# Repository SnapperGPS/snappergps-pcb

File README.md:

> *Are you looking for the open-source SnapperGPS hardware design files? You can find the files for the original version V1.0.0 in this repository and the files for an updated version V2.0.0 [in another repository](https://github.com/SnapperGPS/snappergps-pcb-2). For differences between both versions, please refer to the documentation over there. Jonas, May 2023*

# snappergps-pcb

The SnapperGPS receiver is a small, low-cost, and low-power GNSS receiver for non-real-time wildlife tracking. It employs the snapshot GNSS technology, which offloads the computationally expensive data processing to the cloud, and:

* Measures 32.0 mm x 27.3 mm,

* Operates for more than a year on a tiny 40 mAh battery,

* Has enough memory to provide almost 11,000 position fixes,

* Captures fixes in user-defined time intervals or externally triggered,

* Needs only 12 ms of signal reception for a fix,

* Employs multiple satellite systems for high reliability (GPS, Galileo, and BeiDou),

* Achieves a median real-world tracking accuracy of about 12 m (before smoothing),

* Maintains a real-time clock to accurately timestamp the fixes,

* Measures the temperature in addition, and

* Is configured via USB in your browser without the need to install a driver or an app.

This repository contains the hardware design files that can be used to replicate a SnapperGPS receiver.

If you use SnapperGPS hardware or software for research, please consider citing our publications.

For the hardware:

> Jonas Beuchert, Amanda Matthes, and Alex Rogers. 2023. SnapperGPS: Open Hardware for Energy-Efficient, Low-Cost Wildlife Location Tracking with Snapshot GNSS. Journal of Open Hardware, 7(1): 2, pp. 1–13. [https://doi.org/10.5334/joh.48](https://openhardware.metajnl.com/articles/10.5334/joh.48/).

For the cloud-processing software:

> Jonas Beuchert and Alex Rogers. 2021. SnapperGPS: Algorithms for Energy-Efficient Low-Cost Location Estimation Using GNSS Signal Snapshots. In SenSys ’21: ACM Conference on Embedded Networked Sensor Systems, November, 2021, Coimbra, Portugal. ACM, New York, NY, USA, 13 pages. https://doi.org/10.1145/3485730.3485931.

**Table of Contents**

1. [Workflow](#workflow)

2. [Getting started](#getting-started)

3. [Repository Structure](#repository-structure)

4. [Professional Manufacturing](#professional-manufacturing)

5. [Hand Assembly](#hand-assembly)

6. [Testing](#testing)

7. [Hardware Overview](#hardware-overview)

8. [Pinout](#pinout)

9. [Bill of Materials](#bill-of-materials)

10. [Additional Resources](#additional-resources)

11. [Acknowledgements](#acknowledgements)

## Workflow

- Get/build your SnapperGPS receiver (see sections below).
- [Configure](https://snappergps.info/configure) your SnapperGPS receiver in your browser for your deployment.
- Deploy your SnapperGPS receiver.
- The SnapperGPS receiver captures GNSS snapshots according to your configuration.
- Recover your SnapperGPS receiver.
- [Upload](https://snappergps.info/upload) the data from your SnapperGPS receiver to our server.
- [Download](https://snappergps.info/view) the track of your surveilled animal.

## Getting started

You already have a SnapperGPS receiver? See [here](GETTING-STARTED.md) how to get started.

You need to build one first? Keep reading.

## Repository Structure

The two files `.brd` and `.sch` are CAD files that contain the PCB's board design and schematic, respectively. They have been created with Autodesk EAGLE 9.6.2, but should be compatible with other electronic design software.

The table `.csv` contains the bill of materials (BOM).

The directory `CAMOutputs` includes the Gerber files and drill file, which are necessary for PCB manufacturing.

The two files `.mnb` and `.mnt` can be used for a pick-and-place machine and describe the component positions and orientations on the bottom and top layer, respectively.

## Professional Manufacturing

The simplest way to replicate SnapperGPS is to upload the BOM, the Gerber files, the drill file, and the pick and place files to an online PCB manufacturing and assembly service. They will source the components, print the PCB, and assemble the board.

We recommend a thickness between 0.8 and 1.6 mm for the two-layered board. The substrate can be FR-4 and hot air solder levelling (HASL) or electroless nickel immersion gold (ENIG) can be used for the finish.

You can find an FAQ on professional manufacturing in [the discussions forum](https://github.com/orgs/SnapperGPS/discussions/22).

## Hand Assembly

An alternative to prefessional manufacturing is to just obtain the SnapperGPS PCB from a PCB manufacturer and to manually assembly the board.
Hand-soldering a board takes less than 2 h for a skilled person, but requires intermediate equipment and skills and potentially additional time for testing, debugging, and re-work.

A laser-cut stencil for applying the solder paste can be helpful and can often be ordered together with the PCB.
In addition, the following materials and equipment are required:

* Soldering paste

* Syringe

* Spatula

* Tweezers

* Hot plate, re-flow oven, or hot air gun

* Flux pen (optional, for re-work)

* Multi-meter (optional, for debugging)

Proceed with the following steps to assemble a SnapperGPS PCB:

* Rigidly fix the PCB to a surface with the top layer pointing up.

* Fix the stencil on the PCB.

* Use the syringe to apply solder paste to the stencil.

* Use the spatula to distribute the solder paste such that all pads on the PCB are covered.

* Remove the stencil.

* Check that all pads are covered with solder paste.

* If not, manually apply solder paste.

* Use tweezers to place the components on the PCB.

* Heat the PCB following the re-flow profile of the used solder paste.

* Test the PCB (see below).

* If it does not work, identify problematic PCB sections and re-work, e.g., by applying flux and re-flowing the board. The most common issues are shorts and missing solder paste on some pads, which can be identified by using a multi-meter for continuity testing, but it is also possible that a component is placed incorrectly.

|  | 
|:--:| 
| *Figure 1: Several SnapperGPS PCBs ready for hand assembly.* |

|  | 
|:--:| 
| *Figure 2: A stencil on top of a SnapperGPS PCB with solder paste applied to it.* |

|  | 
|:--:| 
| *Figure 3: A SnapperGPS PCB with solder paste and components on a hot plate while re-flowing.* |

|  | 
|:--:| 
| *Figure 4: An assembled SnapperGPS receiver.* |

|  | 
|:--:| 
| *Figure 5: Measuring the current consumption of an assembled SnapperGPS receiver (bottom left) with a multi-meter (right), a DC voltage source (centre), two jumper wires, and alligator clips.* |

|  | 
|:--:| 
| *Figure 6: Charging a 110 mAh lithium-ion polymer battery via USB with a *SparkFun LiPo Charger Basic*.* |

|  | 
|:--:| 
| *Figure 7: Testing a SnapperGPS receiver with the SnapperGPS app on an Android smartphone using a USB-C cable.* |

## Testing

If you replicated a SnapperGPS receiver yourself, you need to flash the SnapperGPS firmware first:

* Short the VDD pin and the SWCLK pin of the SnapperGPS receiver, e.g., with a paper clip.

* Connect the SnapperGPS receiver via a USB-C cable to a host computer.

* Download [the SnapperGPS firmware binary](https://github.com/SnapperGPS/snappergps-firmware/releases).

* Install [the AudioMoth Flash App](https://github.com/OpenAcousticDevices/AudioMoth-Flash-App/releases) **or** [the Silicon Labs Simplicity Commander](https://community.silabs.com/s/article/simplicity-commander).

* Use one of the two tools two flash the firmware binary to the SnapperGPS receiver. (If you use the AudioMoth Flash App, either use v1.4.0 or, if you use v1.6.0, then disable "Clear User Data When Flashing".)

* Remove the paper clip.

Now, you can continue with some basic testing:

* Open [the SnapperGPS web app](https://snappergps.info) in Microsoft Edge or Google Chrome or download it from [the Microsoft Store](https://apps.microsoft.com/store/detail/snappergps/9P9RPRS6LSMM) or [Google Play](https://play.google.com/store/apps/details?id=com.herokuapp.snapper_gps.twa). (Alternatively, you can also host the SnapperGPS web app yourself, as described in [the _snappergps-app_ repository](https://github.com/SnapperGPS/snappergps-app)).

* Go to the *Configure* page and click/tap on *Pair receiver*.

* The connected SnapperGPS receiver should now be selectable in a pop-up window.

* After pairing, confirm that the receiver information in the table on the top of the page is appropriate, including on-board time and firmware version. The snapshot count should be zero.

* Connect a LiPo battery to the SnapperGPS receiver, paying attention to the polarity markers on top of the PCB. Connect the black cable to the pin next to the *-* and the red cable to the pin next to the *+*.

* Check the measured battery voltage in the table at the top of the *Configure* page. We recommend charging the battery to at least 4.1 V before a long-term deployment.

* Connnect an active GNSS antenna of your choice via the U.FL connector to the SnapperGPS receiver.

* Select some configuration parameters in the app and click/tap on *Configure*.

* Disconnect the SnapperGPS receiver.

* Record a few snapshots outdoors.

* Reconnect the SnapperGPS receiver.

* Go to the *Upload* page and follow the instructions to upload the snapshots from the SnapperGPS receiver to the server. Please select only snapshots for processing that you collected outdoors.

* Once processing is complete, inspect the calculated track on the *Download* page. There are also links to some of our tracks for comparison.

Testing the localisation accuracy:

* Record some data outdoors at a location with known coordinates.

* Upload it via the SnapperGPS app.

* Calculate the horizontal error between the estimated locations and the ground truth.

* We obtained median errors of 10-12 m, depending on the scenario.

Measuring the power consumption:

* Configure a SnapperGPS receiver using the SnapperGPS app.

* Power the SnapperGPS receiver from an external DC source with 3.7-4.2 V.

* Place an ammeter in series with the source.

* The current should be 1-2 μA if the board is sleeping and the maximum current should be around 25 mA when capturing a snapshot. The charge consumption for a single snapshot should be <0.3 μAh.

Testing the flash memory:

* Record the maximum of 10901 snapshots.

* Transfer them to a host computer using the *Transfer data* button on the *Upload* page of the SnapperGPS web app.

* Ensure that all 10901 snapshots have been transferred and are provided as download.

## Hardware Overview

Please have a look at our [paper](https://doi.org/10.5334/joh.48).

## Pinout

We expose the three general-purpose input/output pins (GPIOs) PA0, PA1, and PA2 of the MCU as well as the supply voltage pin VDD and the ground pin GND at an edge of the PCB.
This allows to connect external modules to extend the functionality of the device.
This can be done by soldering wires on the rectangular pads.
For the functionality of the three pins, please refer to [the pinout section in the datasheet of the EFM32HG310](https://www.silabs.com/documents/public/data-sheets/efm32hg-datasheet.pdf#page=118).

We also expose the VDD, GND, RESET, SWCLK, and SWDIO pins of the MCU on the back of the PCB.
The last two ones allow for debugging or flashing using [Serial Wire Debug (SWD)](https://community.silabs.com/s/article/serial-wire-debug-swd-x).
All five circular pads have a spacing of 0.1 in and, hence, the same as common PCB headers.

All ten pads are labelled on the silkscreen of the PCB.

```
Front           │           │ Back
                │           │
                │           │ ○ GND
          VDD □ │           │
                │           │ ○ RESET
    GPIO3/PA2 □ │           │
                │           │ ○ SWCLK
    GPIO2/PA1 □ │           │
                │           │ ○ SWDIO
    GPIO1/PA0 □ │           │
                │           │ ○ VDD
          GND □ │           │
────────────────┘           │
```

## Bill of Materials

|Designator                                    |Qty|Manufacturer                  |Part #                                 |Description/Value                                            |Package/Footprint|Mounting Type|Notes                                                                          |Supplier URL                                                                                           |
|----------------------------------------------|--:|------------------------------|---------------------------------------|-------------------------------------------------------------|-----------------|-------------|-------------------------------------------------------------------------------|-------------------------------------------------------------------------------------------------------|
|C4, C8, C10, C12, C13, C14, C16, C17, C20, C23| 10|Murata                        |GRM155R60J104KA01D                     |Ceramic capacitor, 100 nF                                    |0402             |SMD          |                                                                               |https://www.digikey.com/en/products/detail/murata-electronics/GRM155R60J104KA01D/490-6287-1-ND/3845484 |
|C3, C5, C6, C7, C9                            |  5|Murata                        |GRM155R60J103KA01D                     |Ceramic capacitor, 10 nF                                     |0402             |SMD          |                                                                               |https://www.digikey.com/en/products/detail/murata-electronics/GRM155R60J103KA01D/490-6286-1-ND/3845483 |
|C2                                            |  1|Murata                        |GRM1555C1H101JA01J                     |Ceramic capacitor, 100 pF                                    |0402             |SMD          |                                                                               |https://www.digikey.com/en/products/detail/murata-electronics/GRM1555C1H101JA01J/490-7754-1-ND/4358006 |
|C1                                            |  1|Murata                        |GRM1555C1H220JA01D                     |Ceramic capacitor, 22 pF                                     |0402             |SMD          |                                                                               |https://www.digikey.com/en/products/detail/murata-electronics/GRM1555C1H220JA01D/490-5868-1-ND/3175200 |
|C21, C22                                      |  2|Murata                        |GRM1555C1H180JA01D                     |Ceramic capacitor, 18 pF                                     |0402             |SMD          |                                                                               |https://www.digikey.com/en/products/detail/murata-electronics/GRM1555C1H180JA01D/2854383               |
|C11, C19, C24, C25                            |  4|Murata                        |GRM188R60J105KA01D                     |Multi-layer ceramic capacitor, 1 uF, 6.3 V, X5R              |0603             |SMD          |                                                                               |https://www.digikey.com/en/products/detail/murata-electronics/GRM188R60J105KA01D/490-1550-1-ND/587755  |
|C18                                           |  1|Murata                        |GRM185R60J475ME15D                     |Multi-layer ceramic capacitor, 4.7 uF, 6.3 V, X5R            |0603             |SMD          |                                                                               |https://www.digikey.com/en/products/detail/murata-electronics/GRM185R60J475ME15D/490-3892-1-ND/965934  |
|C15                                           |  1|Murata                        |GRM188R60J106KE47D                     |Multi-layer ceramic capacitor, 10 uF, 6.3 V, X5R             |0603             |SMD          |                                                                               |https://www.digikey.com/en/products/detail/murata-electronics/GRM188R60J106KE47D/490-12538-1-ND/5797528|
|L1                                            |  1|Delta Electronics             |0402HS-390EKTS                        |Fixed inductor, 39 nH, 200 mA, 550 MOhm                      |0402             |SMD          |                                                                               |https://www.digikey.com/en/products/detail/0402HS-390EKTS/2035-0402HS-390EKTSCT-ND/10231211            |
|L2                                            |  1|Murata                        |BLM15HB221SH1D                         |Ferrite bead                                                 |0402             |SMD          |                                                                               |https://www.digikey.com/en/products/detail/murata-electronics/BLM15HB221SH1D/6798444                   |
|R11, R12                                      |  2|Yageo                         |RC0402FR-0715RL                        |Resistor, 15R                                                |0402             |SMD          |                                                                               |https://www.digikey.com/en/products/detail/yageo/RC0402FR-0715RL/311-15LRCT-ND/2827914                 |
|R15, R16                                      |  2|Yageo                         |RC0402FR-071KL                         |Resistor, 1K                                                 |0402             |SMD          |                                                                               |https://www.digikey.com/en/products/detail/yageo/RC0402FR-071KL/726513                                 |
|R10, R13, R17                                 |  3|Yageo                         |RC0402FR-074K7L                        |Resistor, 4K7                                                |0402             |SMD          |                                                                               |https://www.digikey.com/en/products/detail/yageo/RC0402FR-074K7L/311-4-7KLRCT-ND/2827881               |
|R7, R8                                        |  2|Yageo                         |RC0402FR-075K1L                        |Resistor, 5K1                                                |0402             |SMD          |                                                                               |https://www.digikey.com/en/products/detail/yageo/RC0402FR-075K1L/726624                                |
|R18                                           |  1|Yageo                         |RC0402FR-076K8L                        |Resistor, 6K8                                                |0402             |SMD          |                                                                               |https://www.digikey.com/en/products/detail/yageo/RC0402FR-076K8L/311-6-80KLRCT-ND/729589               |
|R14, R19                                      |  2|Yageo                         |RC0402FR-0710KL                        |Resistor, 10K                                                |0402             |SMD          |                                                                               |https://www.digikey.com/en/products/detail/yageo/RC0402FR-0710KL/726523                                |
|R1, R2, R3, R4, R5, R6, R9                    |  7|Yageo                         |RC0402FR-07100KL                       |Resistor, 100K                                               |0402             |SMD          |                                                                               |https://www.digikey.com/en/products/detail/yageo/RC0402FR-07100KL/311-100KLRCT-ND/729473               |
|Q2                                            |  1|Jauch Quartz                  |Q 0,032768-JTX310-12,5-10-T1-HMR-50K-LF|Crystal, 32.768 kHz ±10 ppm, 12.5 pF, 50 kOhm                |2-SMD            |SMD          |Possible substitutes: Epsom, X1A0001410004 FC-135R 32.768KHZ 9PF or Jauch Quartz, Q 0,032768-JTX310-12,5-10-T1-HMR-60K-LF|https://www.digikey.com/en/products/detail/jauch-quartz/Q-0-032768-JTX310-12-5-10-T1-HMR-50K-LF/8108077|
|D1                                            |  1|Rohm Semiconductor            |SML-D12M1WT86                          |LED, yellow-green, 572 nm, 2.2 V                             |0603             |SMD          |                                                                               |https://www.digikey.com/en/products/detail/rohm-semiconductor/SML-D12M1WT86/SML-D12M1WT86CT-ND/5843861 |
|D2                                            |  1|Rohm Semiconductor            |SML-D12U1WT86                          |LED, red, 620 nm, 2.2 V                                      |0603             |SMD          |                                                                               |https://www.digikey.com/en/products/detail/rohm-semiconductor/SML-D12U1WT86/SML-D12U1WT86CT-ND/5843858 |
|TCXO1                                         |  1|Connor Winfield               |D32G-016.368M                          |Temperature compensated oscillator, 16.384 MHz               |3.2x2.5          |SMD          |Possible substitutes: EPSON, X1G005441030112 or TXC Corporation, 7Q-16.368MBG-T|https://www.digikey.com/en/products/detail/connor-winfield/D32G-016-368M/3641696                       |
|U2                                            |  1|Skyworks Solutions Inc.       |SE4150L-R                              |RF receiver                                                  |24-QFN           |SMD          |                                                                               |https://www.digikey.com/en/products/detail/skyworks-solutions-inc/SE4150L-R/863-1354-1-ND/2745473      |
|SAW1                                          |  1|Abracon LLC                   |AFS20A42-1575.42-T3                    |SAW filter, 1.575 GHz, BW 42 MHz                             |4-SMD            |SMD          |Possible substitute: AFS20A02-1575.42-T3                                       |https://www.digikey.com/en/products/detail/abracon-llc/AFS20A42-1575-42-T3/535-12069-1-ND/4075659      |
|U1                                            |  1|Silicon Labs                  |EFM32HG310F64G-C-QFN32R                |Microcontroller                                              |32-QFN           |SMD          |Possible substitutes: EFM32HG310F64G-A-QFN32R or EFM32HG310F64G-B-QFN32R       |https://www.digikey.com/en/products/detail/silicon-labs/EFM32HG310F64G-C-QFN32R/336-6165-1-ND/10314104 |
|U3                                            |  1|Nexperia                      |PRTR5V0U2AX,235                        |TVS diode, 5.5 V                                             |SOT143B          |SMD          |                                                                               |https://www.digikey.com/en/products/detail/nexperia-usa-inc/PRTR5V0U2AX235/1727-5862-1-ND/2698064      |
|IC1                                           |  1|Winbond Electronics           |W25N512GVEIG                           |NAND flash, 512 Mbit                                         |WSON-8           |SMD          |                                                                               |https://www.digikey.com/en/products/detail/W25N512GVEIG/256-W25N512GVEIG-ND/12143334                   |
|J3                                            |  1|TE Connectivity AMP Connectors|1909763-1                              |U.FL connector jack, 50 Ohm                                  |                 |SMD          |                                                                               |https://www.digikey.com/en/products/detail/1909763-1/A118077CT-ND/4729711                              |
|Q1, Q3, Q4                                    |  3|Rohm Semiconductor            |TT8M1TR                                |Mosfet array N and P-channel, 20 V, 2.5 A, 1 W               |8-SMD            |SMD          |                                                                               |https://www.digikey.com/en/products/detail/rohm-semiconductor/TT8M1TR/5042837                          |
|U4                                            |  1|ABLIC U.S.A. Inc.             |S-1318D33-M5T1U4                       |Linear voltage regulator IC, positive fixed, 1 output, 100 mA|SOT-23-5         |SMD          |                                                                               |https://www.digikey.com/en/products/detail/ablic-inc/S-1318D33-M5T1U4/10313979                         |
|J1                                            |  1|JAE Electronics               |DX07S016JA1R1500                       |USB-C receptacle connector, 24 Pins (16+8 dummy), right angle|                 |through-hole |                                                                               |https://www.digikey.com/en/products/detail/jae-electronics/DX07S016JA1R1500/11585731                   |
|J2                                            |  1|JST Sales America Inc.        |S2B-PH-SM4-TB                          |Connector header, right angle, 2 position, 2.00 mm           |                 |SMD          |                                                                               |https://www.digikey.com/en/products/detail/jst-sales-america-inc/S2B-PH-SM4-TB-LF-SN/926655            |
|                                              |   |                              |                                       |                                                             |                 |             |                                                                               |                                                                                                       |

The BOM differs slightly from the one for initial SnapperGPS test boards, which was only $14 in a batch of 100.
For example, we used cheaper TCXOs, the X1G005441030112 manufactured by EPSON or the 7Q-16.368MBG-T from the TXC Corporation, which cost around $2 instead of the expensive D32G-016.368M that costs $7-$8.
We had to introduce this change because of the on-going global supply chain disruptions and recommend to revert to one of the initial choices for replications, if possible, to reduce the overall cost.

## Additional resources

## Acknowledgements

SnapperGPS is developed by
[Jonas Beuchert](https://users.ox.ac.uk/~kell5462/),
[Amanda Matthes](https://amanda-matthes.github.io/), and
[Alex Rogers](https://www.cs.ox.ac.uk/people/alex.rogers/)
in the Department of Computer Science
of the University of Oxford.

Jonas Beuchert and Amanda Matthes are
funded by the EPSRC Centre for Doctoral Training in
Autonomous Intelligent Machines and Systems
(DFT00350-DF03.01, DFT00350-DF03.05) and develop
SnapperGPS as part of their doctoral studies.
The implementation of SnapperGPS 
was co-funded by an EPSRC IAA Technology Fund
(D4D00010-BL14).

[Amanda Matthes](https://github.com/amanda-matthes) owns the copyright of the current SnapperGPS logo/icon that is on the bottom layer silkscreen of the PCB.

##

This documentation is licensed under a
[Creative Commons Attribution 4.0 International License][cc-by].

[![CC BY 4.0][cc-by-image]][cc-by]

[cc-by]: http://creativecommons.org/licenses/by/4.0/
[cc-by-image]: https://i.creativecommons.org/l/by/4.0/88x31.png

SnapperGPS V1.0.0 is certified as open source hardware by the Open Source Hardware Association with UID [UK000044](https://certification.oshwa.org/uk000044.html).

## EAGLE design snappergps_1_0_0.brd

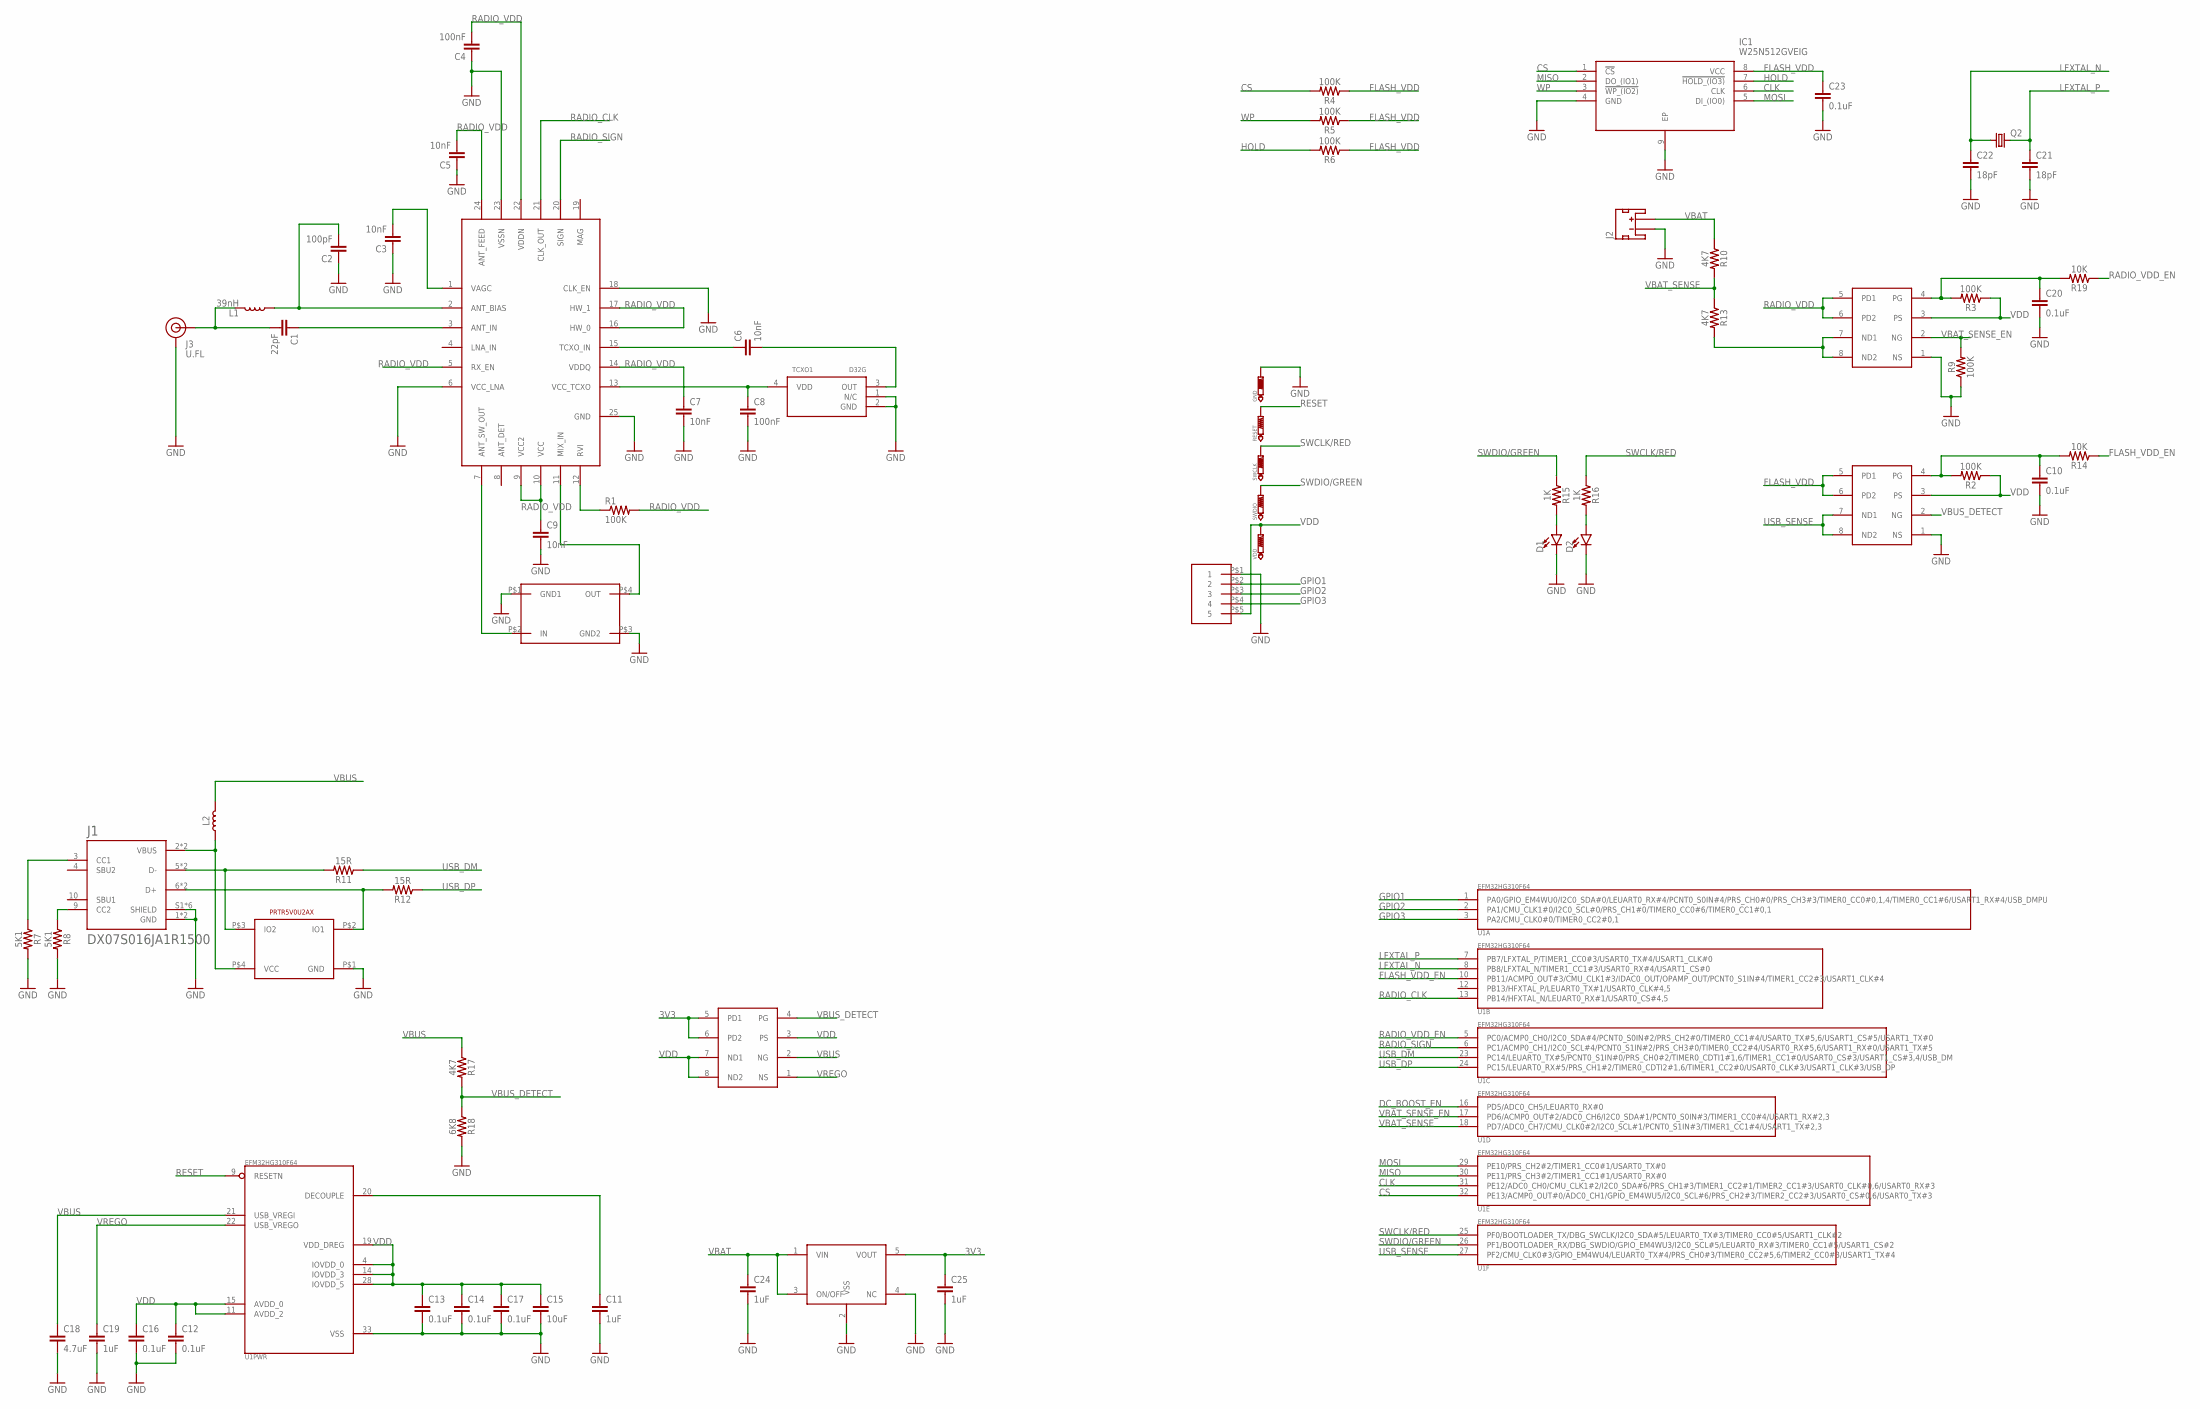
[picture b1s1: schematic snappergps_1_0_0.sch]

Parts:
C1: 22pF; 0402
C2: 100pF; 0402
C3, C5, C6, C7, C9: 10nF; 0402
C4, C8: 100nF; 0402
C10, C12, C13, C14, C16, C17, C20, C23: 0.1uF; 0402
C11, C19, C24, C25: 1uF; 0603
C15: 10uF; 0603
C18: 4.7uF; 0603
C21, C22: 18pF; 0402
D1, D2: LED0603; LED-0603
GND: PTR1B1,27; B1,27
IC1: W25N512GVEIG; SON127P800X600X80-9N
J1: DX07S016JA1R1500; JAE_DX07S016JA1R1500
J2: JST_2MM_MALE; JST-2-SMD
J3: U.FL
L1: 39nH; 0402
L2: INDUCTOR; 0402
Q1, Q3, Q4: TT8M1TRAMANDA; AMANDA_TSST8
Q2: CRYSTAL_JTX310; 3.2X1.5
R1, R2, R3, R4, R5, R6, R9: 100K; 0402
R7, R8: 5K1; 0402
R10, R13, R17: 4K7; 0402
R11, R12: 15R; 0402
R14, R19: 10K; 0402
R15, R16: 1K; 0402
R18: 6K8; 0402
RESET: PTR1B1,27; B1,27
SAW1: SAW_FILTER
SWCLK: PTR1B1,27; B1,27
SWDIO: PTR1B1,27; B1,27
TCXO1: D32G
U1: EFM32HG310F64; QFN32
U2: RF_CIRCUIT-SE4150L; QFN50P400X400X90-25N
U3: TVS_DIODE-PRTR5V0U2AX
U4: S-1318D33-M5T1U4; SOT95P280X145-5N
U5: ALEX_CONN5
VDD: PTR1B1,27; B1,27

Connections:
3V3: C25.1, Q4.5 (PD1), Q4.6 (PD2), U4.5 (VOUT)
CLK: IC1.6 (CLK), U1.31 (PE12/ADC0_CH0/CMU_CLK1#2/I2C0_SDA#6/PRS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)
CS: IC1.1 (!CS), R4.2, U1.32 (PE13/ACMP0_OUT#0/ADC0_CH1/GPIO_EM4WU5/I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)
DC_BOOST_EN: U1.16 (PD5/ADC0_CH5/LEUART0_RX#0)
FLASH_VDD: C23.1, IC1.8 (VCC), Q3.5 (PD1), Q3.6 (PD2), R4.1, R5.1, R6.1
FLASH_VDD_EN: R14.1, U1.10 (PB11/ACMP0_OUT#3/CMU_CLK1#3/IDAC0_OUT/O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)
GND: C2.1, C3.1, C4.1, C5.1, C7.2, C8.2, C9.2, C10.2, C11.2, C12.2, C13.2, C14.2, C15.2, C16.2, C17.2, C18.2, C19.2, C20.2, C21.2, C22.2, C23.2, C24.2, C25.2, D1.C, D2.C, GND.TP, IC1.4 (GND), IC1.9 (EP), J1.1 (GND), J1.12 (GND), J1.S1 (SHIELD), J1.S2 (SHIELD), J1.S3 (SHIELD), J1.S4 (SHIELD), J1.S5 (SHIELD), J1.S6 (SHIELD), J2.1 (-), J3.1 (GND), J3.2 (GND), Q1.1 (NS), Q3.1 (NS), R7.2, R8.2, R9.1, R18.2, SAW1.P$1 (GND1), SAW1.P$3 (GND2), TCXO1.1 (N/C), TCXO1.2 (GND), U1.33 (VSS), U2.6 (VCC_LNA), U2.18 (CLK_EN), U2.23 (VSSN), U2.25 (GND), U3.P$1 (GND), U4.2 (VSS), U4.4 (NC), U5.P$1 (1)
GPIO1: U1.1 (PA0/GPIO_EM4WU0/I2C0_SDA#0/LEUART0_RX#4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), U5.P$2 (2)
GPIO2: U1.2 (PA1/CMU_CLK1#0/I2C0_SCL#0/PRS_CH1#0/TIM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), U5.P$3 (3)
GPIO3: U1.3 (PA2/CMU_CLK0#0/TIMER0_CC2#0,1), U5.P$4 (4)
HOLD: IC1.7 (!HOLD_(IO3)), R6.2
LFXTAL_N: C22.1, Q2.1, U1.8 (PB8/LFXTAL_N/TIMER1_CC1#3/USART0_RX#4/U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)
LFXTAL_P: C21.1, Q2.2, U1.7 (PB7/LFXTAL_P/TIMER1_CC0#3/USART0_TX#4/U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)
MISO: IC1.2 (DO_(IO1)), U1.30 (PE11/PRS_CH3#2/TIMER1_CC1#1/USART0_RX#0)
MIXIN: SAW1.P$4 (OUT), U2.11 (MIX_IN)
MOSI: IC1.5 (DI_(IO0)), U1.29 (PE10/PRS_CH2#2/TIMER1_CC0#1/USART0_TX#0)
unnamed: Q1.7 (ND1), Q1.8 (ND2), R13.2
unnamed: C20.1, Q1.4 (PG), R3.2, R19.2
unnamed: J1.9 (CC2), R8.1
unnamed: J1.3 (CC1), R7.1
unnamed: R1.1, U2.12 (RVI)
unnamed: SAW1.P$2 (IN), U2.7 (ANT_SW_OUT)
unnamed: C8.1, TCXO1.4 (VDD), U2.13 (VCC_TCXO)
unnamed: C6.1, U2.15 (TCXO_IN)
unnamed: C6.2, TCXO1.3 (OUT)
unnamed: C11.1, U1.20 (DECOUPLE)
unnamed: C10.1, Q3.4 (PG), R2.2, R14.2
unnamed: D1.A, R15.2
unnamed: D2.A, R16.2
unnamed: C3.2, U2.1 (VAGC)
unnamed: J1.2 (VBUS), J1.11 (VBUS), L2.1, U3.P$4 (VCC)
unnamed: C2.2, L1.1, U2.2 (ANT_BIAS)
unnamed: C1.1, U2.3 (ANT_IN)
unnamed: C1.2, J3.FEED (SIGNAL), L1.2
unnamed: J1.6 (D+), J1.7 (D+), R12.2, U3.P$2 (IO1)
unnamed: J1.5 (D-), J1.8 (D-), R11.2, U3.P$3 (IO2)
RADIO_CLK: U1.13 (PB14/HFXTAL_N/LEUART0_RX#1/USART0_CS#4,5), U2.21 (CLK_OUT)
RADIO_SIGN: U1.6 (PC1/ACMP0_CH1/I2C0_SCL#4/PCNT0_S1IN#2/P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), U2.20 (SIGN)
RADIO_VDD: C4.2, C5.2, C7.1, C9.1, Q1.5 (PD1), Q1.6 (PD2), R1.2, U2.5 (RX_EN), U2.9 (VCC2), U2.10 (VCC), U2.14 (VDDQ), U2.16 (HW_0), U2.17 (HW_1), U2.22 (VDDN), U2.24 (ANT_FEED)
RADIO_VDD_EN: R19.1, U1.5 (PC0/ACMP0_CH0/I2C0_SDA#4/PCNT0_S0IN#2/P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)
RESET: RESET.TP, U1.9 (RESETN)
SWCLK/RED: R16.1, SWCLK.TP, U1.25 (PF0/BOOTLOADER_TX/DBG_SWCLK/I2C0_SDA#5/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)
SWDIO/GREEN: R15.1, SWDIO.TP, U1.26 (PF1/BOOTLOADER_RX/DBG_SWDIO/GPIO_EM4WU3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)
USB_DM: R11.1, U1.23 (PC14/LEUART0_TX#5/PCNT0_S1IN#0/PRS_CH0#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)
USB_DP: R12.1, U1.24 (PC15/LEUART0_RX#5/PRS_CH1#2/TIMER0_CDTI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)
USB_SENSE: Q3.7 (ND1), Q3.8 (ND2), U1.27 (PF2/CMU_CLK0#3/GPIO_EM4WU4/LEUART0_TX#4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)
VBAT: C24.1, J2.2 (+), R10.1, U4.1 (VIN), U4.3 (ON/OFF)
VBAT_SENSE: R10.2, R13.1, U1.18 (PD7/ADC0_CH7/CMU_CLK0#2/I2C0_SCL#1/PCNT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)
VBAT_SENSE_EN: Q1.2 (NG), R9.2, U1.17 (PD6/ACMP0_OUT#2/ADC0_CH6/I2C0_SDA#1/PCN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)
VBUS: C18.1, L2.2, Q4.2 (NG), R17.1, U1.21 (USB_VREGI)
VBUS_DETECT: Q3.2 (NG), Q4.4 (PG), R17.2, R18.1
VDD: C12.1, C13.1, C14.1, C15.1, C16.1, C17.1, Q1.3 (PS), Q3.3 (PS), Q4.3 (PS), Q4.7 (ND1), Q4.8 (ND2), R2.1, R3.1, U1.4 (IOVDD_0), U1.11 (AVDD_2), U1.14 (IOVDD_3), U1.15 (AVDD_0), U1.19 (VDD_DREG), U1.28 (IOVDD_5), U5.P$5 (5), VDD.TP
VREGO: C19.1, Q4.1 (NS), U1.22 (USB_VREGO)
WP: IC1.3 (!WP_(IO2)), R5.2

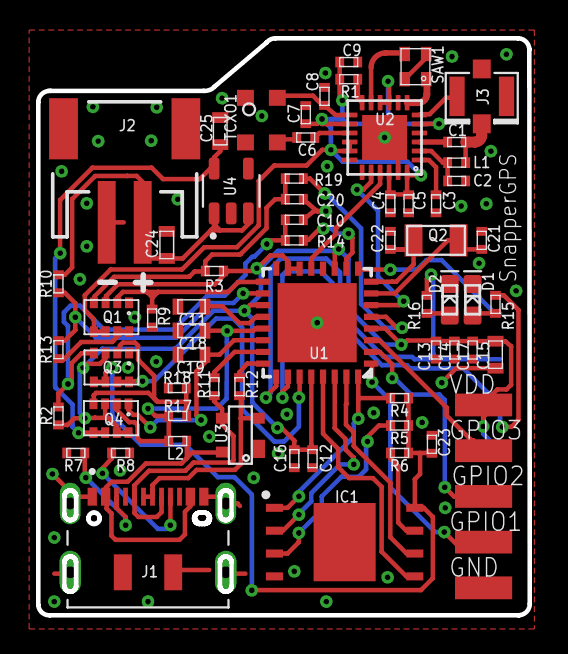
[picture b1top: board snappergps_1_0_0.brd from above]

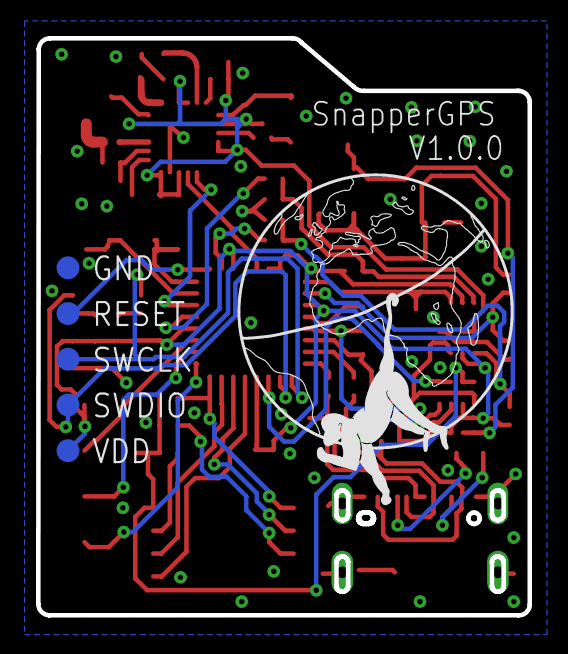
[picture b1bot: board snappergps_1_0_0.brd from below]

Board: 2 copper layers, 27.3 x 32.1 mm, 68 parts (5 on the bottom side), 53 nets.

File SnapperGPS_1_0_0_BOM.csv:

Designator,Qty,Manufacturer,Part #,Description/Value,Package/Footprint,Mounting Type,Notes,Supplier URL,Price (1 set) [USD],Price (100 sets) [USD],Price (1000 sets) [USD]
"C4, C8, C10, C12, C13, C14, C16, C17, C20, C23",10,Murata,GRM155R60J104KA01D,"Ceramic capacitor, 100 nF",402,SMD,,https://www.digikey.com/en/products/detail/murata-electronic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,0.33,14.6,81.7
"C3, C5, C6, C7, C9",5,Murata,GRM155R60J103KA01D,"Ceramic capacitor, 10 nF",402,SMD,,https://www.digikey.com/en/products/detail/murata-electronic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,0.5,4.43,29.1
C2,1,Murata,GRM1555C1H101JA01J,"Ceramic capacitor, 100 pF",402,SMD,,https://www.digikey.com/en/products/detail/murata-electronic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,0.1,0.81,4.54
C1,1,Murata,GRM1555C1H220JA01D,"Ceramic capacitor, 22 pF",402,SMD,,https://www.digikey.com/en/products/detail/murata-electronic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,0.1,0.81,4.57
"C21, C22",2,Murata,GRM1555C1H180JA01D,"Ceramic capacitor, 18 pF",402,SMD,,https://www.digikey.com/en/products/detail/murata-electronic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,0.2,2.32,13
"C11, C19, C24, C25",4,Murata,GRM188R60J105KA01D,"Multi-layer ceramic capacitor, 1 uF, 6.3 V, X5R",603,SMD,,https://www.digikey.com/en/products/detail/murata-electronic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,0.4,11,61.84
C18,1,Murata,GRM185R60J475ME15D,"Multi-layer ceramic capacitor, 4.7 uF, 6.3 V, X5R",603,SMD,,https://www.digikey.com/en/products/detail/murata-electronic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,0.3,11.67,72.02
C15,1,Murata,GRM188R60J106KE47D,"Multi-layer ceramic capacitor, 10 uF, 6.3 V, X5R",603,SMD,,https://www.digikey.com/en/products/detail/murata-electronic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,0.15,5.07,29.44
L1,1,Delta Electronics,0402HS-390EKTS,"Fixed inductor, 39 nH, 200 mA, 550 MOhm",402,SMD,,https://www.digikey.com/en/products/detail/0402HS-390EKTS/20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,0.26,15.68,109.72
L2,1,Murata,BLM15HB221SH1D,Ferrite bead,402,SMD,,https://www.digikey.com/en/products/detail/murata-electronic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,0.1,4.36,25.08
"R11, R12",2,Yageo,RC0402FR-0715RL,"Resistor, 15R",402,SMD,,https://www.digikey.com/en/products/detail/yageo/RC0402FR-07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,0.2,1.32,5.98
"R15, R16",2,Yageo,RC0402FR-071KL,"Resistor, 1K",402,SMD,,https://www.digikey.com/en/products/detail/yageo/RC0402FR-07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,0.2,1.32,5.98
"R10, R13, R17",3,Yageo,RC0402FR-074K7L,"Resistor, 4K7",402,SMD,,https://www.digikey.com/en/products/detail/yageo/RC0402FR-07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,0.3,1.98,7.77
"R7, R8",2,Yageo,RC0402FR-075K1L,"Resistor, 5K1",402,SMD,,https://www.digikey.com/en/products/detail/yageo/RC0402FR-07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,0.2,1.32,5.98
R18,1,Yageo,RC0402FR-076K8L,"Resistor, 6K8",402,SMD,,https://www.digikey.com/en/products/detail/yageo/RC0402FR-07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,0.1,0.66,2.99
"R14, R19",2,Yageo,RC0402FR-0710KL,"Resistor, 10K",402,SMD,,https://www.digikey.com/en/products/detail/yageo/RC0402FR-07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,0.2,1.32,5.98
"R1, R2, R3, R4, R5, R6, R9",7,Yageo,RC0402FR-07100KL,"Resistor, 100K",402,SMD,,https://www.digikey.com/en/products/detail/yageo/RC0402FR-07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,0.7,4.62,14.98
Q2,1,Jauch Quartz,"Q 0,032768-JTX310-12,5-10-T1-HMR-50K-LF","Ctystal, 32.768 kHz ±10 ppm, 12.5 pF, 50 kOhm",2-SMD,SMD,"Possible substitute: Epsom, X1A0001410004 FC-135R 32.768KHZ 9PF",https://www.digikey.com/en/products/detail/jauch-quartz/Q-0-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,0.86,62.7,495
D1,1,Rohm Semiconductor,SML-D12M1WT86,"LED, yellow-green, 572 nm, 2.2 V",603,SMD,,https://www.digikey.com/en/products/detail/rohm-semiconducto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,0.22,5.51,39.86
D2,1,Rohm Semiconductor,SML-D12U1WT86,"LED, red, 620 nm, 2.2 V",603,SMD,,https://www.digikey.com/en/products/detail/rohm-semiconducto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,0.22,5.51,39.86
TCXO1,1,Connor Winfield,D32G-016.368M,"Temperature compensated oscillator, 16.384 MHz",3.2x2.5,SMD,"Possible substitutes: EPSON, X1G005441030112 or TXC Corporation, 7Q-16.368MBG-T",https://www.digikey.com/en/products/detail/connor-winfield/D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,8,700,7000
U2,1,Skyworks Solutions Inc.,SE4150L-R,RF receiver,24-QFN,SMD,,https://www.digikey.com/en/products/detail/skyworks-solution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,0.86,86.4,864
SAW1,1,Abracon LLC,AFS20A42-1575.42-T3,"SAW filter, 1.575 GHz, BW 42 MHz",4-SMD,SMD,,https://www.digikey.com/en/products/detail/abracon-llc/AFS20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,1.05,71.37,543.74
U1,1,Silicon Labs,EFM32HG310F64G-C-QFN32R,Microcontroller,32-QFN,SMD,,https://www.digikey.com/en/products/detail/silicon-labs/EFM3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,5.91,435.04,3703.46
U3,1,Nexperia,"PRTR5V0U2AX,235","TVS diode, 5.5 V",SOT143B,SMD,,https://www.digikey.com/en/products/detail/nexperia-usa-inc/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,0.66,42.47,257.87
IC1,1,Winbond Electronics,W25N512GVEIG,"NAND flash, 512 Mbit",WSON-8,SMD,,https://www.digikey.com/en/products/detail/W25N512GVEIG/256-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,2.9,228.68,2051.92
J3,1,TE Connectivity AMP Connectors,1909763-1,"U.FL connector jack, 50 Ohm",,SMD,,https://www.digikey.com/en/products/detail/1909763-1/A118077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,0.51,36.55,595.9
"Q1, Q3, Q4",3,Rohm Semiconductor,TT8M1TR,"Mosfet array N and P-channel, 20 V, 2.5 A, 1 W",8-SMD,SMD,,https://www.digikey.com/en/products/detail/rohm-semiconducto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,1.56,86.58,487.08
U4,1,ABLIC U.S.A. Inc.,S-1318D33-M5T1U4,"Linear voltage regulator IC, positive fixed, 1 output, 100 mA",SOT-23-5,SMD,,https://www.digikey.com/en/products/detail/ablic-inc/S-1318D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,1.58,109.94,908.2
J1,1,JAE Electronics,DX07S016JA1R1500,"USB-C receptacle connector, 24 Pins (16+8 dummy), right angle",,through-hole,,https://www.digikey.com/en/products/detail/jae-electronics/D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,1.67,129.65,1080.44
J2,1,JST Sales America Inc.,S2B-PH-SM4-TB,"Connector header, right angle, 2 position, 2.00 mm",,SMD,,https://www.digikey.com/en/products/detail/jst-sales-america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,0.54,39.08,339.84
,,,,,,,,,31.55,2124.54,18900.69

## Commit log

2022-06-07 Add hardware and hardware docs
2022-06-08 Add note regarding antenna attachment
2022-06-08 Increment version number
2022-06-20 Add PCB manufacturing parameters; add acknowledgement for image
    Remove white space
2022-07-04 Add workflow; add info on substitutes to BOM; restructure; tweak white space; change battery
2022-07-12 Update URL
2022-07-12 Update link to firmware release
2022-07-14 Add link to preprint to readme
2022-07-19 Mention smoothing in readme
2022-07-22 Add references, fix table of contents
2022-07-22 Tweak references
2022-08-10 Mention snappergps-app repository in readme
    In response to https://github.com/orgs/SnapperGPS/discussions/3
2022-08-18 Add getting started
2022-08-21 Update issue templates
    Create troubleshooting issue template
2022-08-23 updated photos
2022-08-23 updated image text in GETTING-STARTED.md
2022-08-23 Remove number
2022-08-25 Add links
2022-08-25 Add picture showing incorrect JST-PH connector
2022-08-25 Re-phrase troubleshooting template
2022-08-25 Add link to issues
2022-09-30 Add funding statement
2022-10-03 Make funding statement more precise
2022-10-14 Add note on shortening the board
2022-11-23 Add CC license to readme
2022-11-23 Add CC-BY license to getting-started
2022-11-23 Tweak layout
2022-11-26 Fix grammar in readme
2022-11-29 Add OSHW label
2022-11-29 Fix white space
2022-12-28 Fix spelling mistake
2023-01-18 Add another antenna
2023-01-18 Add another substitute for Q2 and fix typo
    Substitute tested by @amanda-matthes.
2023-02-10 Update citation
2023-02-10 Harden paper link
2023-04-25 Update hyperlink
2023-04-26 Add link to manufacturing FAQ
2023-04-26 Fix typo
2023-05-12 Add link to new repository
2023-12-03 Update README.md with note on unusable AudioMoth Flash App version
2025-08-21 Update README.md with SAW filter sub

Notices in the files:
README.md:
[Amanda Matthes](https://github.com/amanda-matthes) owns the copyright of the current SnapperGPS logo/icon that is on the bottom layer silkscreen of the PCB.
This documentation is licensed under a
[Creative Commons Attribution 4.0 International License][cc-by].
CC BY 4.0
parts and their libraries:
SparkFun-Connectors: Licensing: Creative Commons ShareAlike 4.0 International - https://creativecommons.org/licenses/by-sa/4.0
EFM32: CC0 License
